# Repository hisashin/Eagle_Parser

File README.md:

Eagle_Parser
============

EAGLE lbr&amp;brd&amp;sch file parser

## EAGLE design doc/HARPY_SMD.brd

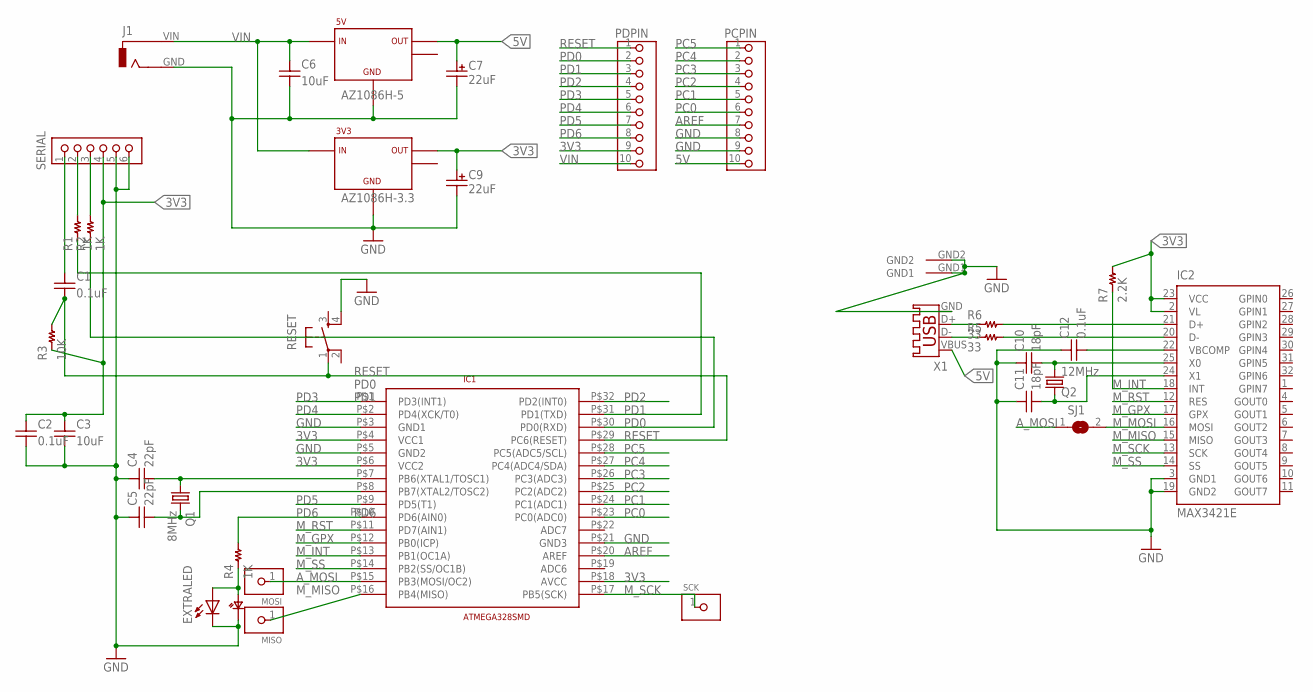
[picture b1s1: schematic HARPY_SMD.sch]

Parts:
3V3, 5V: AZ1086H
C1, C2, C12: 0.1uF; SMD_2012_0805
C3: 10uF; SMD_2012_0805
C4, C5: 22pF; SMD_2012_0805
C6: 10uF; SMD_3216_1206
C7, C9: 22uF; SMD_3528
C10, C11: 18pF; SMD_2012_0805
EXTRALED: LED3MM
IC1: ATMEGA328SMD
IC2: MAX3421E; TQFP44
J1: DCJ0303
LED: LED1608; SMD_1608_0603
MISO: 1X0108S; 1X01_0.8_UNSIGNED_SQUARE
MOSI: 1X0108S; 1X01_0.8_UNSIGNED_SQUARE
PCPIN: 1X10; 1X10_1.1_UNSIGNED
PDPIN: 1X10; 1X10_1.1_UNSIGNED
Q1: 8MHz; HC49U-V
Q2: 12MHz; HC49U-V
R1, R2, R4: 1K; SMD_2012_0805
R3: 10K; SMD_2012_0805
R5, R6: 33; SMD_2012_0805
R7: 2.2K; SMD_2012_0805
RESET: 10-XXAKI; TSKB-2JL
SCK: 1X0108S; 1X01_0.8_UNSIGNED_SQUARE
SERIAL: 1X06A; 1X06_1.1_ARROW
SJ1: SJ
X1: USB-A003

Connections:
3V3: 3V3.OUTPUT1, C2.P$1 (1), C3.P$1 (1), C9.P$1 (+), IC1.P$4 (VCC1), IC1.P$6 (VCC2), IC1.P$18 (AVCC), IC2.2 (VL), IC2.23 (VCC), PDPIN.9, R3.P$1 (1), R7.P$2 (2), SERIAL.4
5V: 5V.OUTPUT1, C7.P$1 (+), PCPIN.10, X1.VBUS (1)
AREF: IC1.P$20 (AREF), PCPIN.7
A_MOSI: IC1.P$15 (PB3(MOSI/OC2)), MOSI.1, SJ1.1
GND: 3V3.GND, 5V.GND, C2.P$2 (2), C3.P$2 (2), C4.P$1 (1), C5.P$1 (1), C6.P$2 (2), C7.P$2 (-), C9.P$2 (-), C10.P$1 (1), C11.P$1 (1), C12.P$1 (1), EXTRALED.K (C), IC1.P$3 (GND1), IC1.P$5 (GND2), IC1.P$21 (GND3), IC2.3 (GND1), IC2.19 (GND2), J1.GND, LED.P$2 (C), PCPIN.8, PCPIN.9, RESET.4 (S1), SERIAL.5, SERIAL.6, X1.GND (4), X1.GND1, X1.GND2
M_GPX: IC1.P$12 (PB0(ICP)), IC2.17 (GPX)
M_INT: IC1.P$13 (PB1(OC1A)), IC2.18 (INT), R7.P$1 (1)
M_MISO: IC1.P$16 (PB4(MISO)), IC2.15 (MISO), MISO.1
M_MOSI: IC2.16 (MOSI), SJ1.2
M_RST: IC1.P$11 (PD7(AIN1)), IC2.12 (RES)
M_SCK: IC1.P$17 (PB5(SCK)), IC2.13 (SCK), SCK.1
M_SS: IC1.P$14 (PB2(SS/OC1B)), IC2.14 (SS)
unnamed: C1.P$1 (1), SERIAL.1
unnamed: R1.P$2 (2), SERIAL.2
unnamed: R2.P$2 (2), SERIAL.3
unnamed: EXTRALED.A, LED.P$1 (A), R4.P$1 (1)
unnamed: C4.P$2 (2), IC1.P$7 (PB6(XTAL1/TOSC1)), Q1.1
unnamed: C5.P$2 (2), IC1.P$8 (PB7(XTAL2/TOSC2)), Q1.2
unnamed: R6.P$1 (1), X1.D+ (3)
unnamed: R5.P$1 (1), X1.D- (2)
unnamed: IC2.21 (D+), R6.P$2 (2)
unnamed: IC2.20 (D-), R5.P$2 (2)
unnamed: C10.P$2 (2), IC2.25 (X0), Q2.1
unnamed: C11.P$2 (2), IC2.24 (X1), Q2.2
unnamed: C12.P$2 (2), IC2.22 (VBCOMP)
PC0: IC1.P$23 (PC0(ADC0)), PCPIN.6
PC1: IC1.P$24 (PC1(ADC1)), PCPIN.5
PC2: IC1.P$25 (PC2(ADC2)), PCPIN.4
PC3: IC1.P$26 (PC3(ADC3)), PCPIN.3
PC4: IC1.P$27 (PC4(ADC4/SDA)), PCPIN.2
PC5: IC1.P$28 (PC5(ADC5/SCL)), PCPIN.1
PD0: IC1.P$30 (PD0(RXD)), PDPIN.2, R2.P$1 (1)
PD1: IC1.P$31 (PD1(TXD)), PDPIN.3, R1.P$1 (1)
PD2: IC1.P$32 (PD2(INT0)), PDPIN.4
PD3: IC1.P$1 (PD3(INT1)), PDPIN.5
PD4: IC1.P$2 (PD4(XCK/T0)), PDPIN.6
PD5: IC1.P$9 (PD5(T1)), PDPIN.7
PD6: IC1.P$10 (PD6(AIN0)), PDPIN.8, R4.P$2 (2)
RESET: C1.P$2 (2), IC1.P$29 (PC6(RESET)), PDPIN.1, R3.P$2 (2), RESET.1
VIN: 3V3.INPUT, 5V.INPUT, C6.P$1 (1), J1.VIN, PDPIN.10

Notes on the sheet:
AZ1086H-3.3
AZ1086H-5

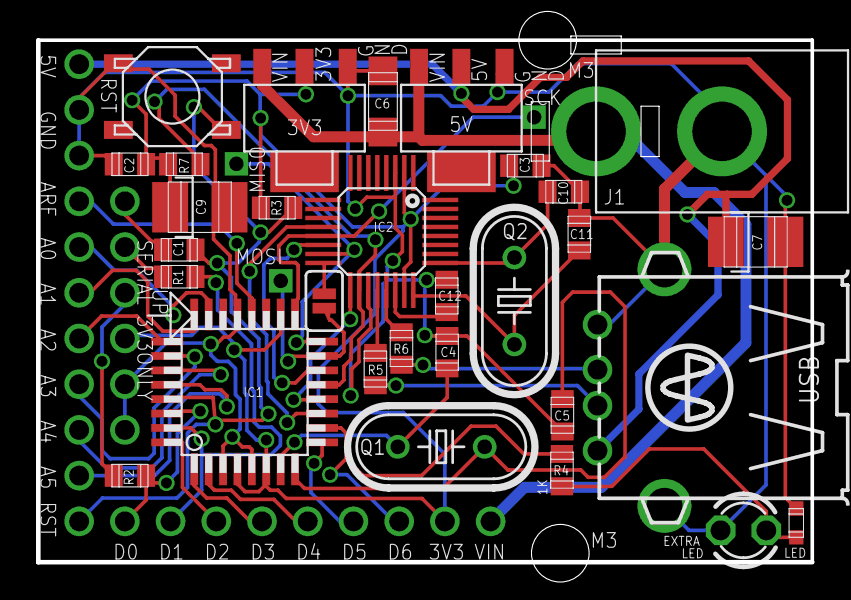
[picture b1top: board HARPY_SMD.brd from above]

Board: 2 copper layers, 43.0 x 29.1 mm, 37 parts (0 on the bottom side), 40 nets.

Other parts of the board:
U$1: LOLI_BNAMES_0.5

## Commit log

2012-10-28 start develop
2012-10-28 EAGLE version 6.3.0
2012-10-28 parse with SAX
2012-10-28 Entity enum added
2012-10-28 DTD coding
2012-10-29 DTD coding end
2012-10-29 start parsing
2012-10-30 HasTextInterface,HasAttrInterface complete
2012-10-30 successfull parsing.start to draw with JMagick.
2012-10-30 override all toString
2012-11-01 draw first lines
2012-11-02 wire draw complete
2012-11-02 start touching dru
2012-11-02 dru parsing
2012-11-02 apply dru to pad
2012-11-02 proper color selected
2012-11-02 fixing draw
2012-11-02 handle stroke-linecap
2012-11-03 strange act of stroke-linecap round
2012-11-03 dru parse
2012-11-04 success to rotate text
2012-11-04 treat text
2012-12-03 trying to manage pattern
2012-12-15 test
